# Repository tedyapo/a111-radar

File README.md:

# a111-radar
Sensor module using A111 60 GHz radar

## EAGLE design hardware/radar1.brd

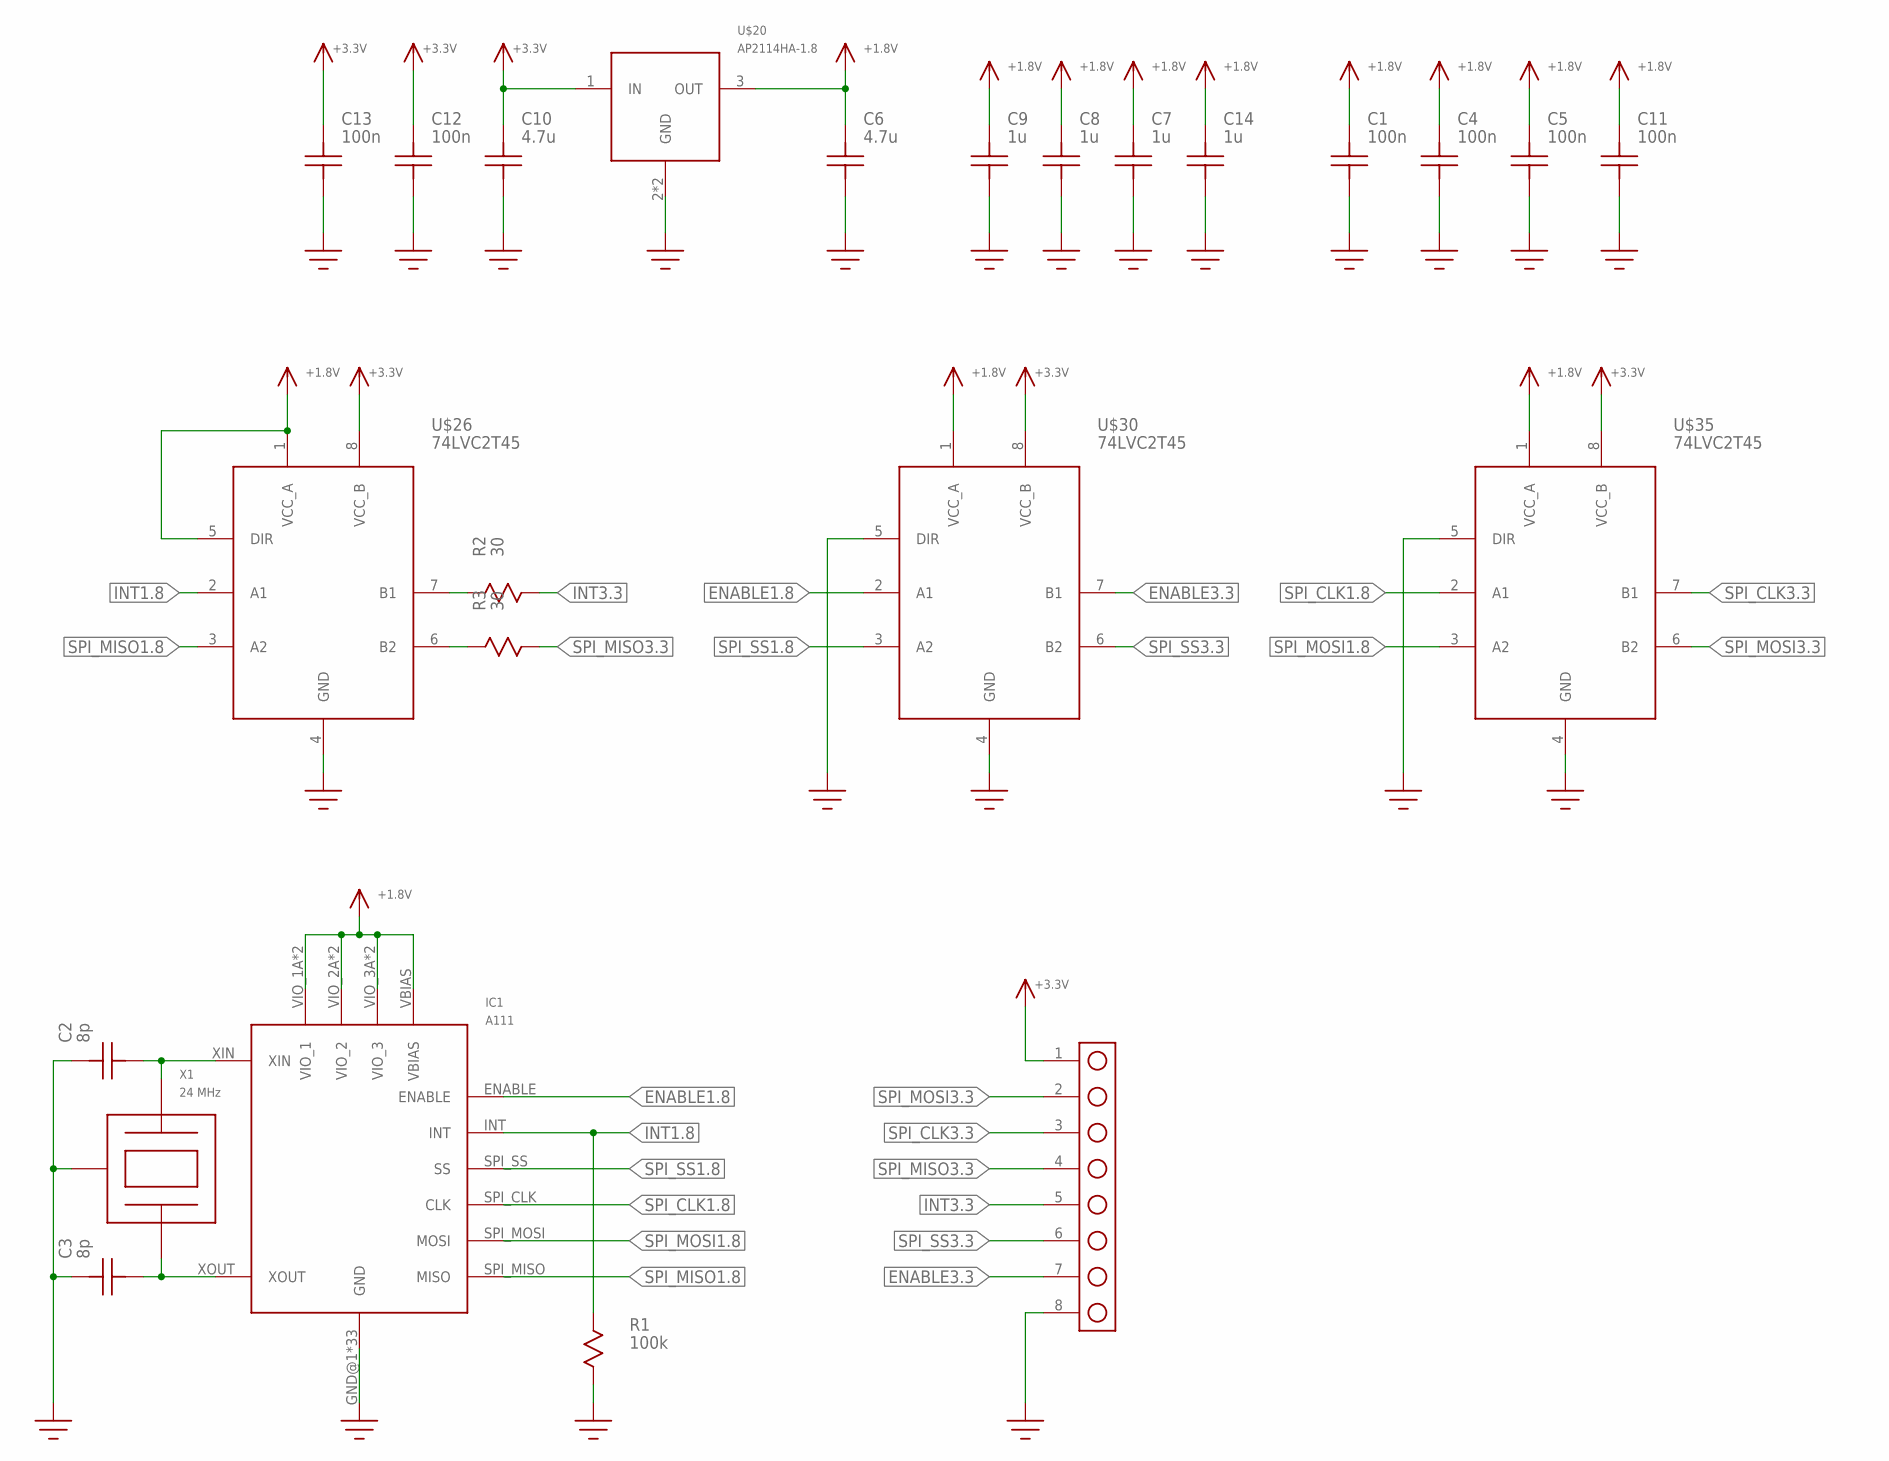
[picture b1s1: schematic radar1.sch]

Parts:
C1, C4, C5, C11, C12, C13: 100n; C0402
C2, C3: 8p; C0402
C6: 4.7u; C0603
C7, C8, C9, C14: 1u; C0603
C10: 4.7u; 1206
IC1: A111
J1: HEADER_8_PIN
R1: 100k; R0603
R2, R3: 30; R0603
U$20: AP2114HA-1.8; SOT-223
U$26, U$30, U$35: 74LVC2T45; SM8
X1: 24 MHz; CRYSTAL_3.2X2.5

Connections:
+1.8V: C1.2, C4.2, C5.2, C6.P$2, C7.P$2, C8.P$2, C9.P$2, C11.2, C14.P$2, IC1.VBIAS, IC1.VIO_1A (VIO_1), IC1.VIO_1B (VIO_1), IC1.VIO_2A (VIO_2), IC1.VIO_2B (VIO_2), IC1.VIO_3A (VIO_3), IC1.VIO_3B (VIO_3), U$20.3 (OUT), U$26.1 (VCC_A), U$26.5 (DIR), U$30.1 (VCC_A), U$35.1 (VCC_A)
+3.3V: C10.P$2, C12.2, C13.2, J1.1, U$20.1 (IN), U$26.8 (VCC_B), U$30.8 (VCC_B), U$35.8 (VCC_B)
ENABLE1.8: IC1.ENABLE, U$30.2 (A1)
ENABLE3.3: J1.7, U$30.7 (B1)
GND: C1.1, C2.2, C3.2, C4.1, C5.1, C6.P$1, C7.P$1, C8.P$1, C9.P$1, C10.P$1, C11.1, C12.1, C13.1, C14.P$1, IC1.GND@1 (GND), IC1.GND@2 (GND), IC1.GND@3 (GND), IC1.GND@4 (GND), IC1.GND@5 (GND), IC1.GND@6 (GND), IC1.GND@7 (GND), IC1.GND@8 (GND), IC1.GND@9 (GND), IC1.GND@10 (GND), IC1.GND@11 (GND), IC1.GND@12 (GND), IC1.GND@13 (GND), IC1.GND@14 (GND), IC1.GND@15 (GND), IC1.GND@16 (GND), IC1.GND@17 (GND), IC1.GND@18 (GND), IC1.GND@19 (GND), IC1.GND@20 (GND), IC1.GND@21 (GND), IC1.GND@22 (GND), IC1.GND@23 (GND), IC1.GND@24 (GND), IC1.GND@25 (GND), IC1.GND@26 (GND), IC1.GND@27 (GND), IC1.GND@28 (GND), IC1.GND@29 (GND), IC1.GND@30 (GND), IC1.GND@31 (GND), IC1.GND@32 (GND), IC1.GND@33 (GND), J1.8, R1.P$2, U$20.2 (GND), U$20.4 (GND), U$26.4 (GND), U$30.4 (GND), U$30.5 (DIR), U$35.4 (GND), U$35.5 (DIR), X1.P$2 (P$CASE), X1.P$4 (P$CASE)
INT1.8: IC1.INT, R1.P$1, U$26.2 (A1)
INT3.3: J1.5, R2.P$2
unnamed: C2.1, IC1.XIN, X1.P$1 (P$X1)
unnamed: C3.1, IC1.XOUT, X1.P$3 (P$X2)
unnamed: R2.P$1, U$26.7 (B1)
unnamed: R3.P$1, U$26.6 (B2)
SPI_CLK1.8: IC1.SPI_CLK (CLK), U$35.2 (A1)
SPI_CLK3.3: J1.3, U$35.7 (B1)
SPI_MISO1.8: IC1.SPI_MISO (MISO), U$26.3 (A2)
SPI_MISO3.3: J1.4, R3.P$2
SPI_MOSI1.8: IC1.SPI_MOSI (MOSI), U$35.3 (A2)
SPI_MOSI3.3: J1.2, U$35.6 (B2)
SPI_SS1.8: IC1.SPI_SS (SS), U$30.3 (A2)
SPI_SS3.3: J1.6, U$30.6 (B2)

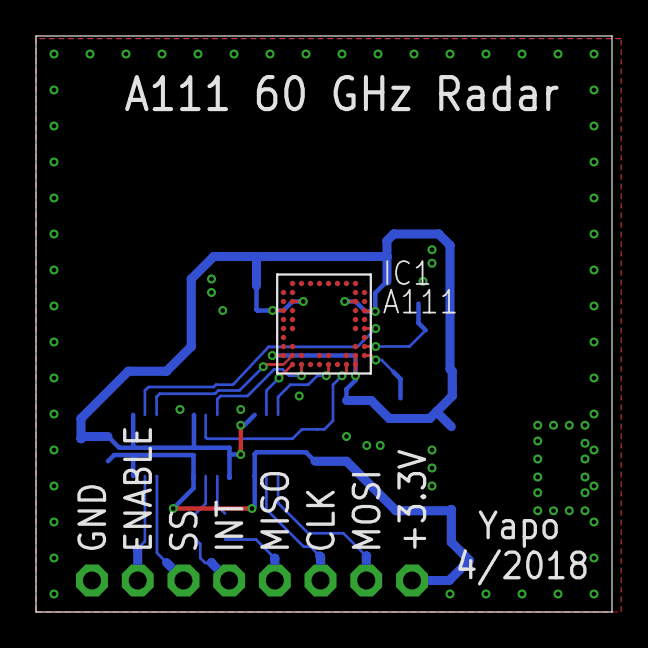
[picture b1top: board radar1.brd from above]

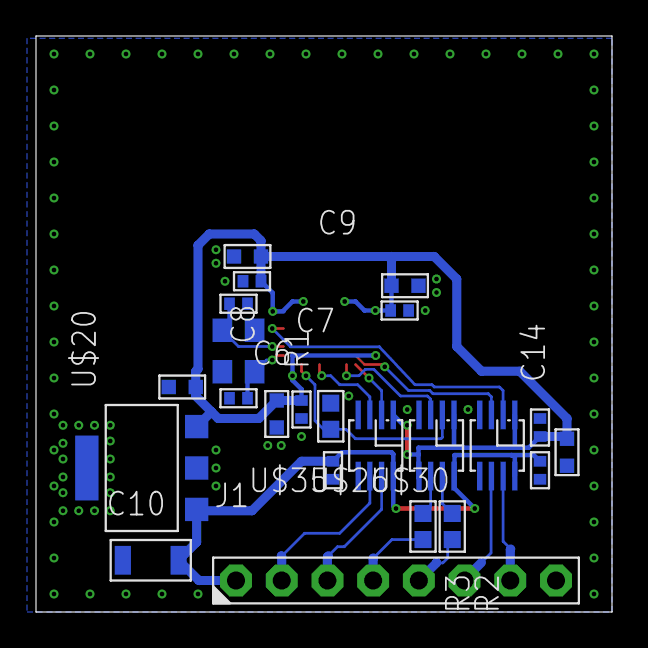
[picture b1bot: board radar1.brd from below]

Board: 2 copper layers, 32.0 x 32.0 mm, 24 parts (23 on the bottom side), 19 nets.

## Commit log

2018-04-27 initial checkin
